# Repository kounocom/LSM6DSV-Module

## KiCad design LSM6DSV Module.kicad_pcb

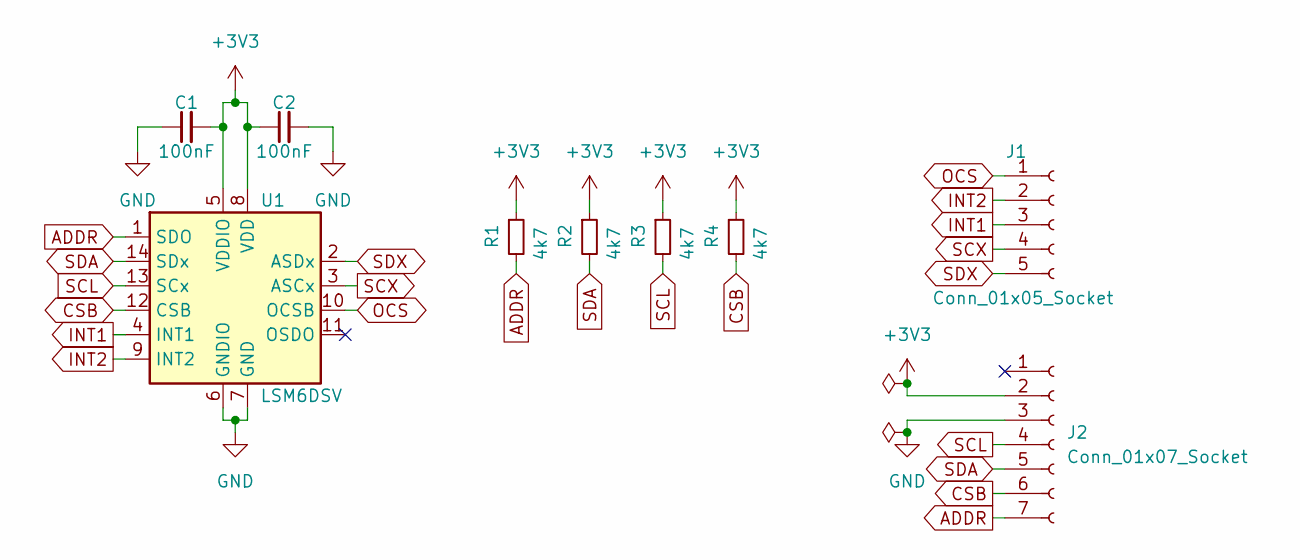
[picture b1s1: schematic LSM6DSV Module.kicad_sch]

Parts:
C1, C2: 100nF; C_0603_1608Metric; MPN C14663
J1: Conn_01x05_Socket; PinHeader_1x05_P2.54mm_Vertical
J2: Conn_01x07_Socket; PinHeader_1x07_P2.54mm_Vertical
R1, R2, R3, R4: 4k7; R_0603_1608Metric; MPN C23162
U1: LSM6DSV; Bosch_LGA-14_3x2.5mm_P0.5mm; MPN C5267406

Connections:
+3V3: C1.2, C2.1, J2.2, R1.1, R2.1, R3.1, R4.1, U1.5 (VDDIO), U1.8 (VDD)
ADDR: J2.7, R1.2, U1.1 (SDO)
CSB: J2.6, R4.2, U1.12 (CSB)
GND: C1.1, C2.2, J2.3, U1.6 (GNDIO), U1.7 (GND)
INT1: J1.3, U1.4 (INT1)
INT2: J1.2, U1.9 (INT2)
OCS: J1.1, U1.10 (OCSB)
SCL: J2.4, R3.2, U1.13 (SCx)
SCX: J1.4, U1.3 (ASCx)
SDA: J2.5, R2.2, U1.14 (SDx)
SDX: J1.5, U1.2 (ASDx)

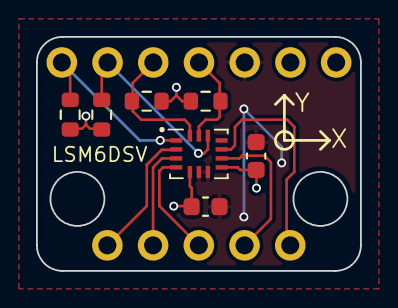
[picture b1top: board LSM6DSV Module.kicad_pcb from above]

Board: 2 copper layers, 18.0 x 13.0 mm, 9 parts (0 on the bottom side), 11 nets.

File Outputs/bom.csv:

Designator,Footprint,Quantity,Value,LCSC Part #
"C1, C2",603,2,100nF,C14663
"R1, R2, R3, R4",603,4,4k7,C23162
U1,Bosch_LGA-14_3x2.5mm_P0.5mm,1,LSM6DSV,C5267406

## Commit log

2023-11-20 waaaaaaat
2023-11-20 remove pinheaders from cpl file
2023-11-20 added 5x2 panel files
2023-11-20 fucking farming commits at this point
